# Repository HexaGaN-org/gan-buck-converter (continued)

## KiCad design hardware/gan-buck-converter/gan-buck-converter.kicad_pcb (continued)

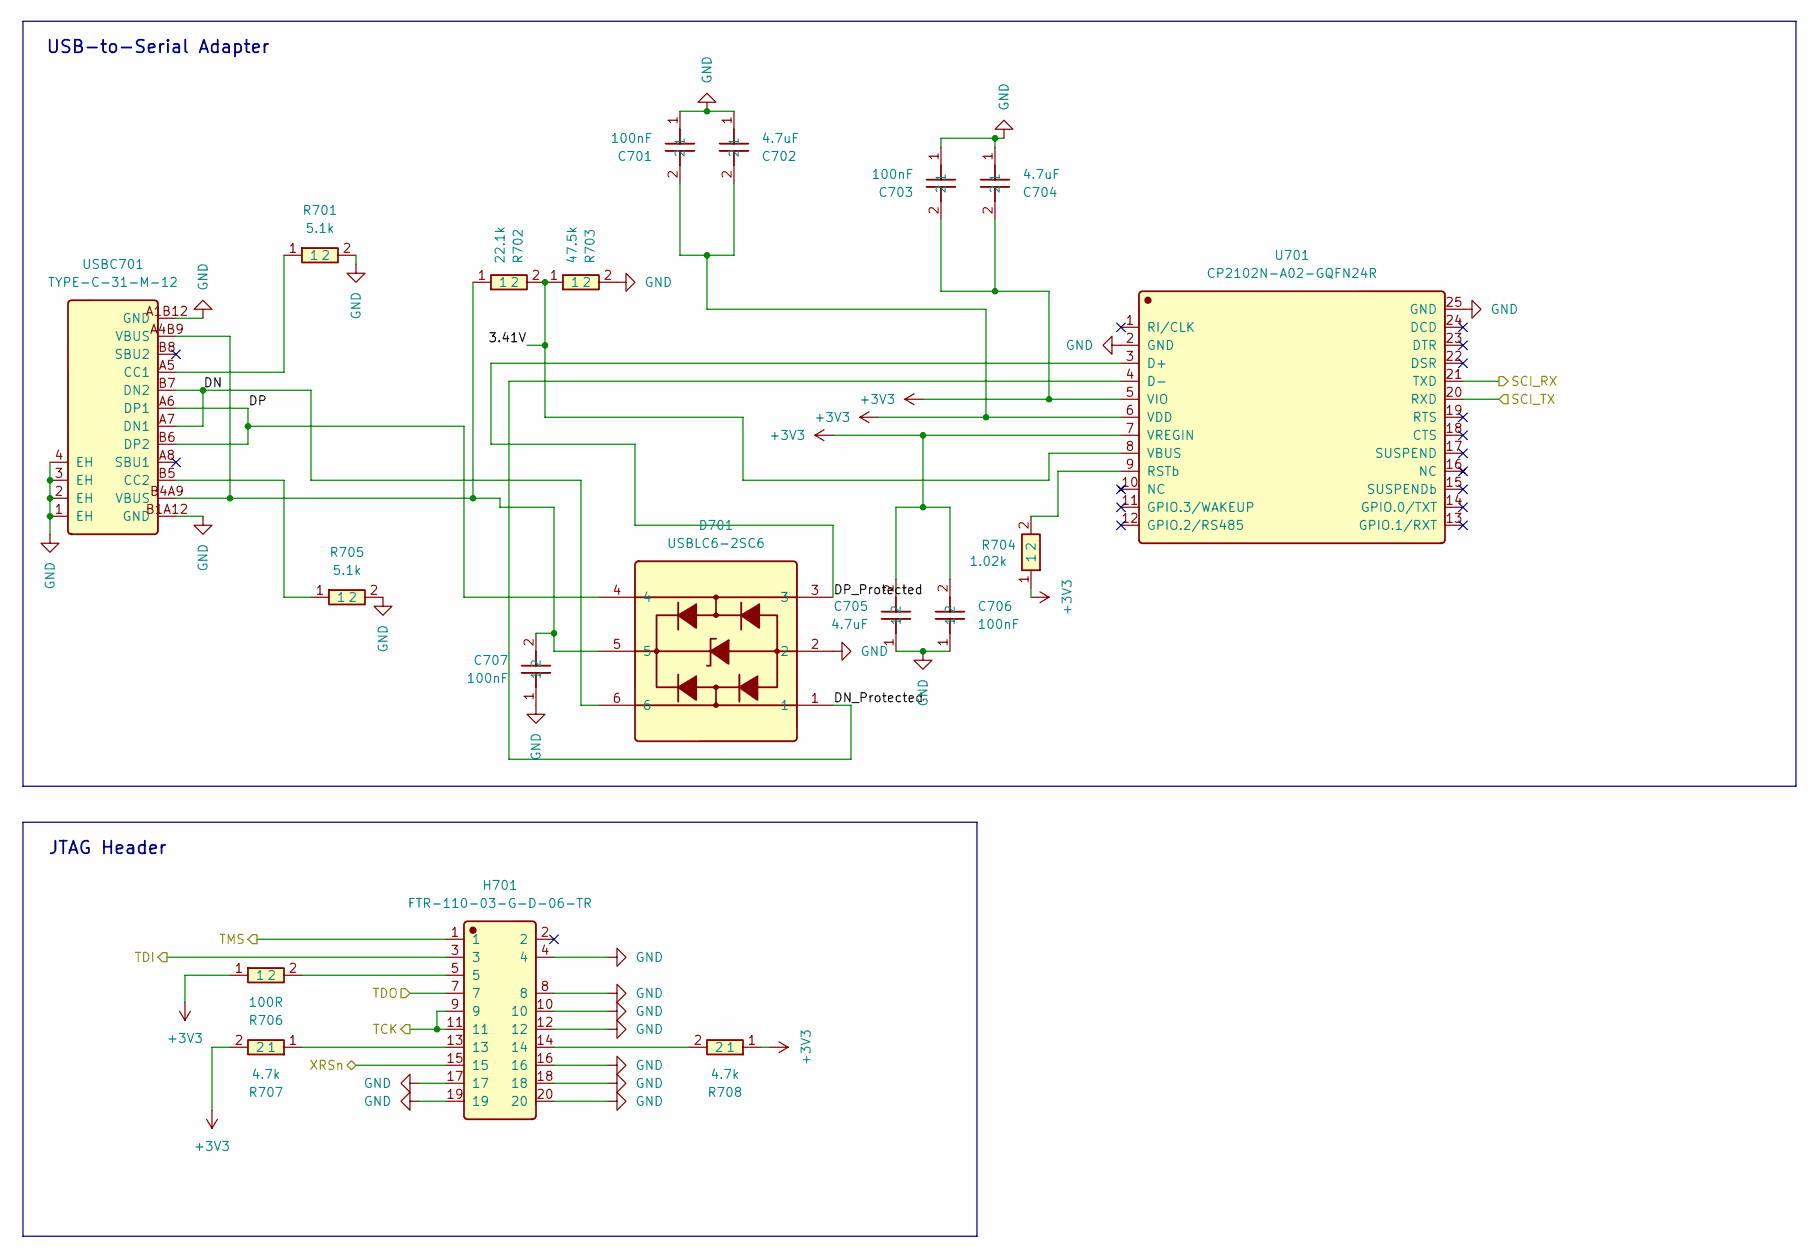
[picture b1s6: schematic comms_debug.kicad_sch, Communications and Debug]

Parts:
C701, C703, C706, C707: 100nF; CC0603KRX7R9BB104; Manufacturer Part CC0603KRX7R9BB104; LCSC C14663
C702, C704, C705: 4.7uF; CL10B475KQ8NQNC; Manufacturer Part CL10B475KQ8NQNC; LCSC C107368
D701: USBLC6-2SC6; SC-74-6_1.55x2.9mm_P0.95mm; Manufacturer Part USBLC6-2SC6; LCSC C7519
H701: FTR-110-03-G-D-06-TR; Manufacturer Part FTR-110-03-G-D-06-TR; LCSC C3332048
R701, R705: 5.1k; 0603WAF5101T5E; Manufacturer Part 0603WAF5101T5E; LCSC C23186
R702: 22.1k; 0603WAF2212T5E; Manufacturer Part 0603WAF2212T5E; LCSC C25961
R703: 47.5k; 0603WAF4752T5E; Manufacturer Part 0603WAF4752T5E; LCSC C23061
R704: 1.02k; RT0603BRD071K02L; Manufacturer Part RT0603BRD071K02L; LCSC C705734
R706: 100R; 0603WAF1000T5E; Manufacturer Part 0603WAF1000T5E; LCSC C22775
R707, R708: 4.7k; RCT034K7JLF; Manufacturer Part RCT034K7JLF; LCSC C177333
U701: CP2102N-A02-GQFN24R; CP2102N_QFN24_4x4mm_P0.5mm_EP2.55x2.55mm; Manufacturer Part CP2102N-A02-GQFN24R; LCSC C969151
USBC701: TYPE-C-31-M-12; Manufacturer Part TYPE-C-31-M-12; LCSC C165948

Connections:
+3V3: C701.2, C702.2, C703.2, C704.2, C705.2, C706.2, R704.1, R706.1, R707.2, R708.1, U701.5 (VIO), U701.6 (VDD), U701.7 (VREGIN); also elsewhere on the board
/Comms and Debug/3.41V: R702.2, R703.1, U701.8 (VBUS)
/Comms and Debug/DN: D701.6, USBC701.A7 (DN1), USBC701.B7 (DN2)
/Comms and Debug/DN_Protected: D701.1, U701.4 (D-)
/Comms and Debug/DP: D701.4, USBC701.A6 (DP1), USBC701.B6 (DP2)
/Comms and Debug/DP_Protected: D701.3, U701.3 (D+)
/Comms and Debug/SCI_RX: U701.21 (TXD); also elsewhere on the board
/Comms and Debug/SCI_TX: U701.20 (RXD); also elsewhere on the board
/Comms and Debug/TCK: H701.9, H701.11; also elsewhere on the board
/Comms and Debug/TDI: H701.3; also elsewhere on the board
/Comms and Debug/TDO: H701.7; also elsewhere on the board
/Comms and Debug/TMS: H701.1; also elsewhere on the board
/Comms and Debug/XRSn: H701.15; also elsewhere on the board
GND: C701.1, C702.1, C703.1, C704.1, C705.1, C706.1, C707.1, D701.2, H701.4, H701.8, H701.10, H701.12, H701.16, H701.17, H701.18, H701.19, H701.20, R701.2, R703.2, R705.2, U701.2 (GND), U701.25 (GND), USBC701.1 (EH), USBC701.2 (EH), USBC701.3 (EH), USBC701.4 (EH), USBC701.A1B12 (GND), USBC701.B1A12 (GND); also elsewhere on the board
unnamed: C707.2, D701.5, R702.1, USBC701.A4B9 (VBUS), USBC701.B4A9 (VBUS)
unnamed: H701.5, R706.2
unnamed: H701.13, R707.1
unnamed: H701.14, R708.2
unnamed: R704.2, U701.9 (RSTb)
unnamed: R701.1, USBC701.A5 (CC1)
unnamed: R705.1, USBC701.B5 (CC2)

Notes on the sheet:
JTAG Header
USB-to-Serial Adapter

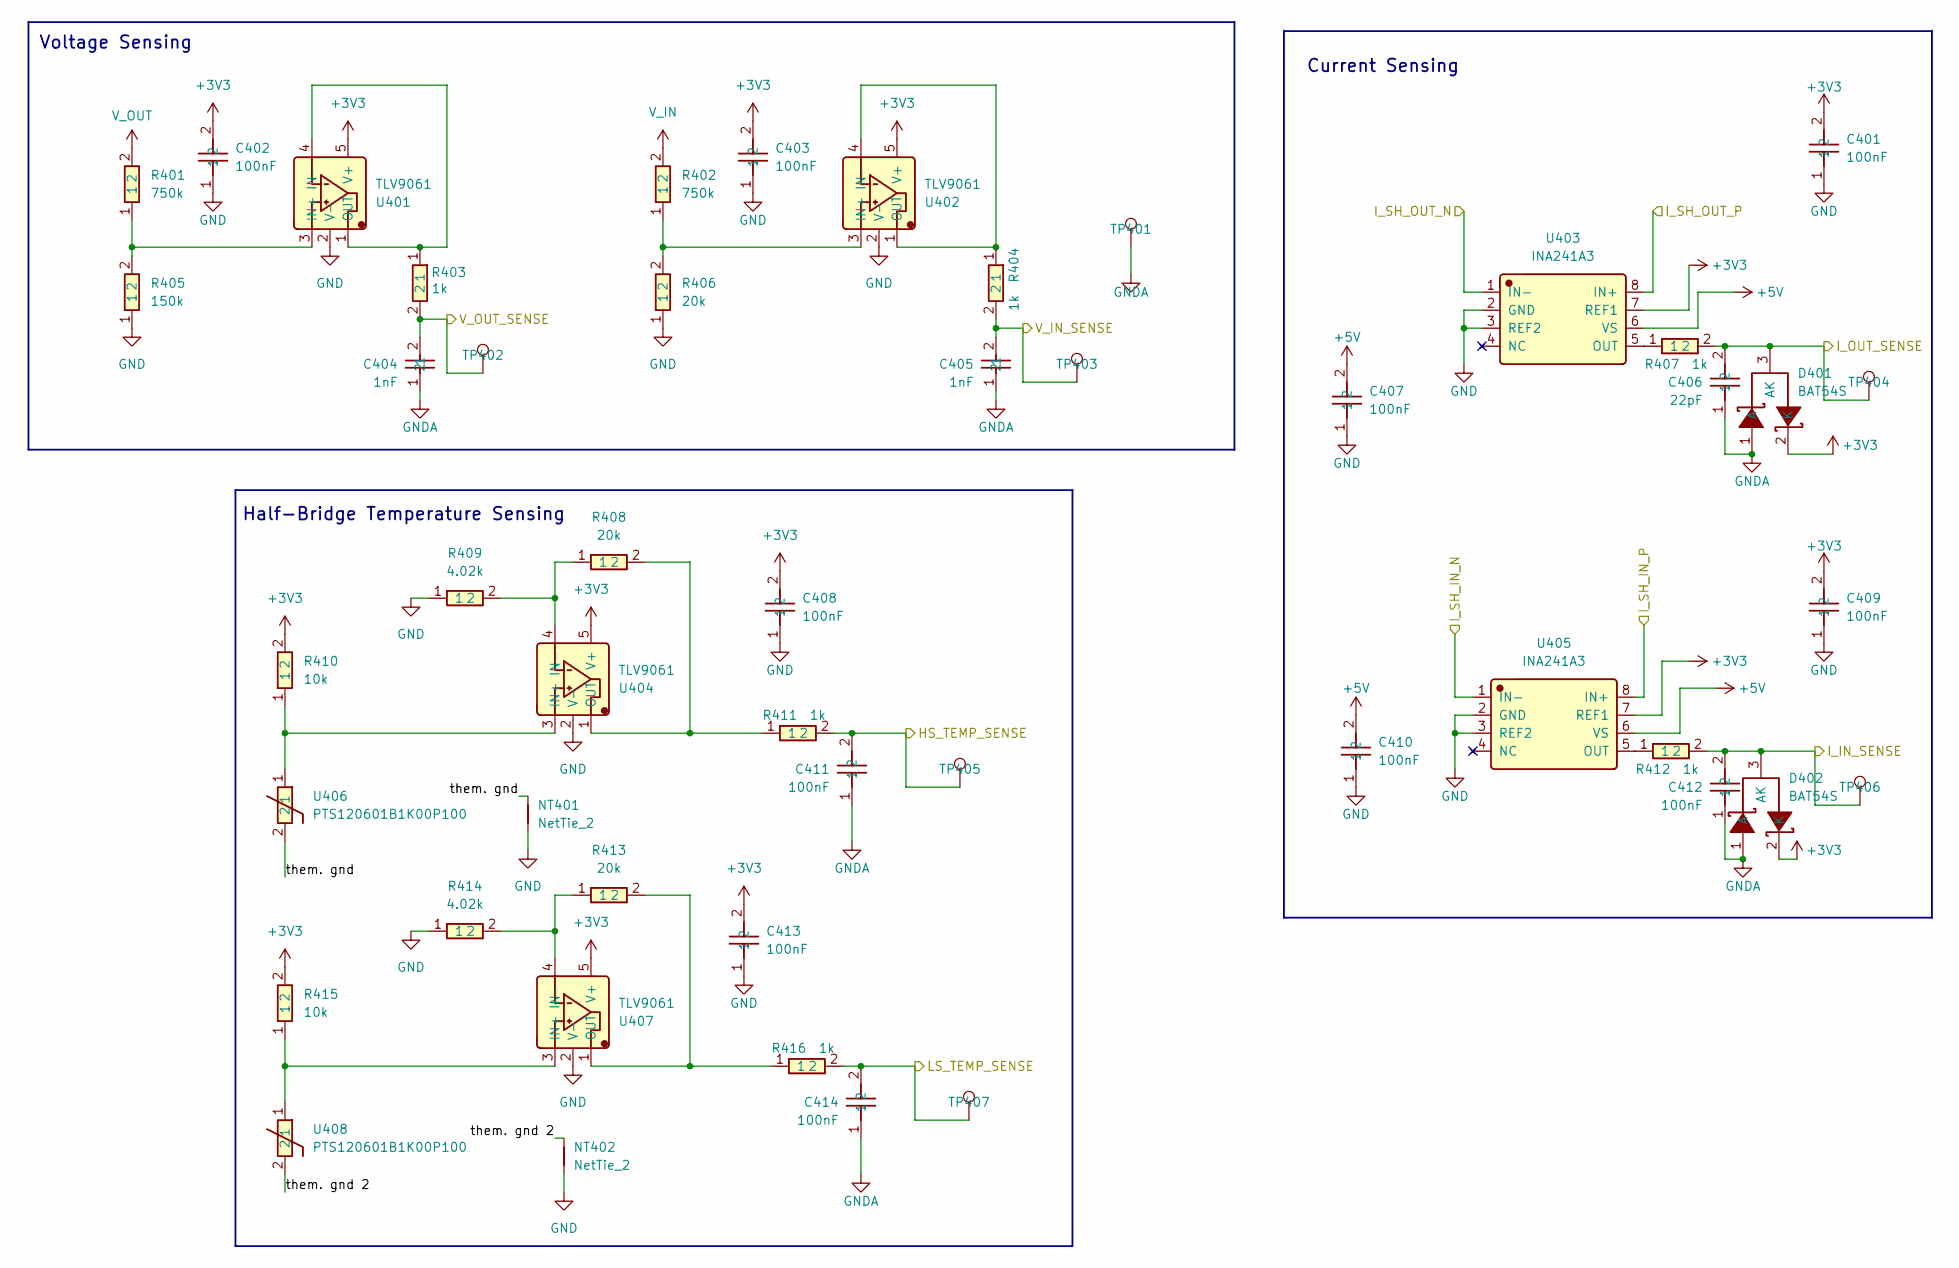
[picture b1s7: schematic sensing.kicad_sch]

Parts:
C401, C402, C403, C407, C408, C409, C410, C411, C412, C413, C414: 100nF; CC0603KRX7R9BB104; Manufacturer Part CC0603KRX7R9BB104; LCSC C14663
C404, C405: 1nF; CL10B102KB8NNNC; Manufacturer Part CL10B102KB8NNNC; LCSC C1588
C406: 22pF; CL10C220JB8NNNC; Manufacturer Part CL10C220JB8NNNC; LCSC C1653
D401, D402: BAT54S; BAT54S_215; Manufacturer Part BAT54S,215; LCSC C47546
NT401, NT402: NetTie_2; NetTie-2_SMD_Pad0.5mm
R401, R402: 750k; 1206W4F7503T5E; Manufacturer Part 1206W4F7503T5E; LCSC C25835
R403, R404, R407, R411, R412, R416: 1k; 0603WAF1001T5E; Manufacturer Part 0603WAF1001T5E; LCSC C21190
R405: 150k; 0603WAF1503T5E; Manufacturer Part 0603WAF1503T5E; LCSC C22807
R406, R408, R413: 20k; 0603WAF2002T5E; Manufacturer Part 0603WAF2002T5E; LCSC C4184
R409, R414: 4.02k; 0603WAF4021T5E_C23040; Manufacturer Part 0603WAF4021T5E; LCSC C23040
R410, R415: 10k; 0603WAF1002T5E; Manufacturer Part 0603WAF1002T5E; LCSC C25804
TP401: GNDA; TestPoint_Pad_D2.0mm
TP402: V_OUT_SENSE; TestPoint_Pad_D2.0mm
TP403: V_IN_SENSE; TestPoint_Pad_D2.0mm
TP404: I_OUT_SENSE; TestPoint_Pad_D2.0mm
TP405: HS_TEMP_SENSE; TestPoint_Pad_D2.0mm
TP406: I_IN_SENSE; TestPoint_Pad_D2.0mm
TP407: LS_TEMP_SENSE; TestPoint_Pad_D2.0mm
U401, U402, U404, U407: TLV9061; TLV9061IDBVR; Manufacturer Part TLV9061IDBVR; LCSC C398358
U403, U405: INA241A3; INA241A3IDDFR; Manufacturer Part INA241A3IDDFR; LCSC C6051860
U406, U408: PTS120601B1K00P100; Vishay_PTS1206; Manufacturer Part PTS120601B1K00P100; LCSC C141528

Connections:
+3V3: C401.2, C402.2, C403.2, C408.2, C409.2, C413.2, D401.2 (K), D402.2 (K), R410.2, R415.2, U401.5 (V+), U402.5 (V+), U403.7 (REF1), U404.5 (V+), U405.7 (REF1), U407.5 (V+); also elsewhere on the board
+5V: C407.2, C410.2, U403.6 (VS), U405.6 (VS); also elsewhere on the board
/Input Supply/I_SH_IN_N: U405.1 (IN-); also elsewhere on the board
/Input Supply/I_SH_IN_P: U405.8 (IN+); also elsewhere on the board
/Microcontroller/HS_TEMP_SENSE: C411.2, R411.2, TP405.1 (1_1); also elsewhere on the board
/Microcontroller/I_IN_SENSE: C412.2, D402.3 (AK), R412.2, TP406.1 (1_1); also elsewhere on the board
/Microcontroller/I_OUT_SENSE: C406.2, D401.3 (AK), R407.2, TP404.1 (1_1); also elsewhere on the board
/Microcontroller/LS_TEMP_SENSE: C414.2, R416.2, TP407.1 (1_1); also elsewhere on the board
/Microcontroller/V_IN_SENSE: C405.2, R404.2, TP403.1 (1_1); also elsewhere on the board
/Microcontroller/V_OUT_SENSE: C404.2, R403.2, TP402.1 (1_1); also elsewhere on the board
/Power Stage/I_SH_OUT_N: U403.1 (IN-); also elsewhere on the board
/Power Stage/I_SH_OUT_P: U403.8 (IN+); also elsewhere on the board
/Sensing/them. gnd: NT401.2, U406.2
/Sensing/them. gnd 2: NT402.2, U408.2
GND: C401.1, C402.1, C403.1, C407.1, C408.1, C409.1, C410.1, C413.1, NT401.1, NT402.1, R405.1, R406.1, R409.1, R414.1, U401.2 (V-), U402.2 (V-), U403.2 (GND), U403.3 (REF2), U404.2 (V-), U405.2 (GND), U405.3 (REF2), U407.2 (V-); also elsewhere on the board
GNDA: C404.1, C405.1, C406.1, C411.1, C412.1, C414.1, D401.1 (A), D402.1 (A), TP401.1 (1_1); also elsewhere on the board
unnamed: R401.1, R405.2, U401.3 (IN+)
unnamed: R403.1, U401.1 (OUT), U401.4 (IN-)
unnamed: R402.1, R406.2, U402.3 (IN+)
unnamed: R404.1, U402.1 (OUT), U402.4 (IN-)
unnamed: R407.1, U403.5 (OUT)
unnamed: R410.1, U404.3 (IN+), U406.1
unnamed: R408.1, R409.2, U404.4 (IN-)
unnamed: R408.2, R411.1, U404.1 (OUT)
unnamed: R412.1, U405.5 (OUT)
unnamed: R415.1, U407.3 (IN+), U408.1
unnamed: R413.1, R414.2, U407.4 (IN-)
unnamed: R413.2, R416.1, U407.1 (OUT)
V_IN: R402.2; also elsewhere on the board
V_OUT: R401.2; also elsewhere on the board

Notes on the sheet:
Voltage Sensing
Current Sensing
Half-Bridge Temperature Sensing

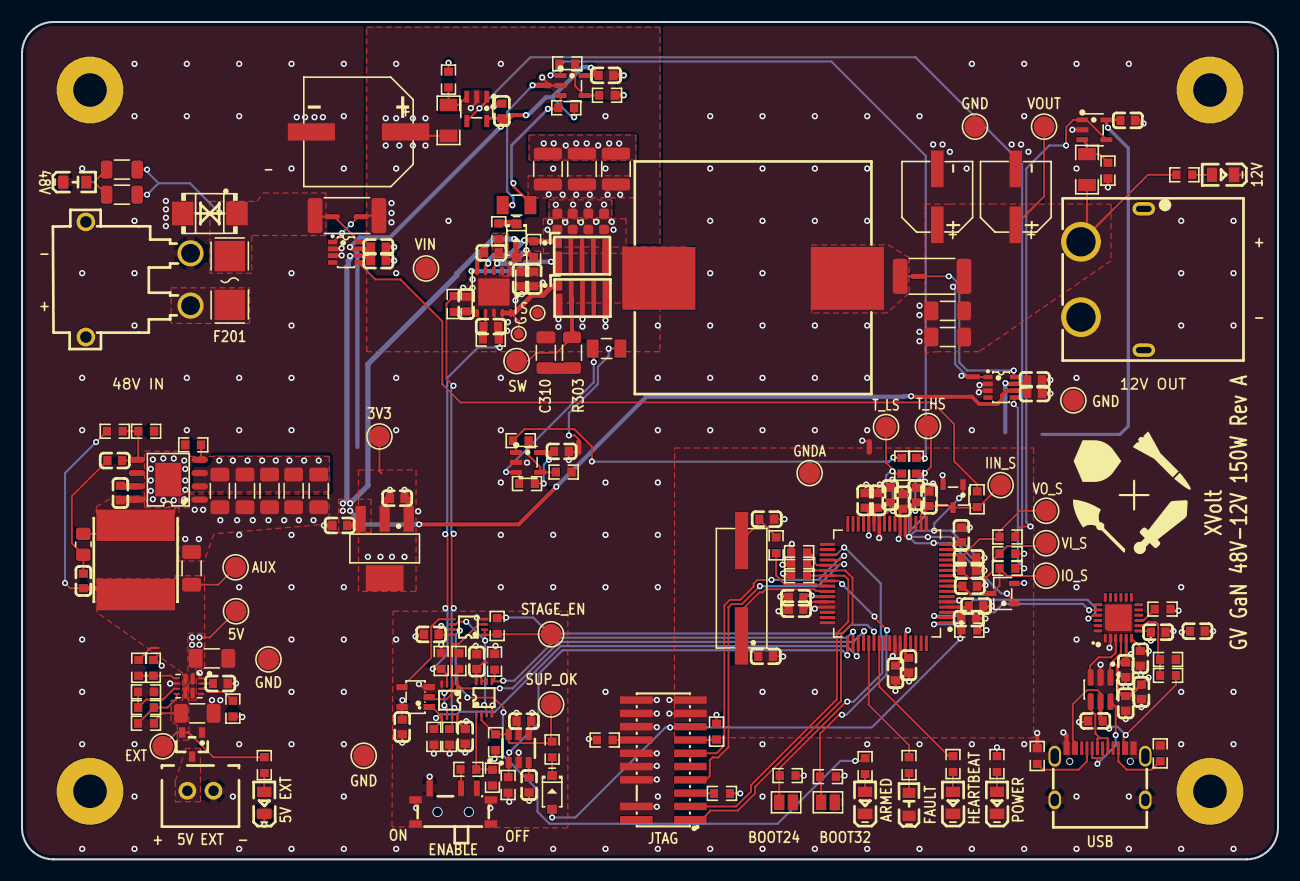
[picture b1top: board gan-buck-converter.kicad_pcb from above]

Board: 4 copper layers, 120.0 x 80.0 mm, 218 parts (0 on the bottom side), 110 nets.
